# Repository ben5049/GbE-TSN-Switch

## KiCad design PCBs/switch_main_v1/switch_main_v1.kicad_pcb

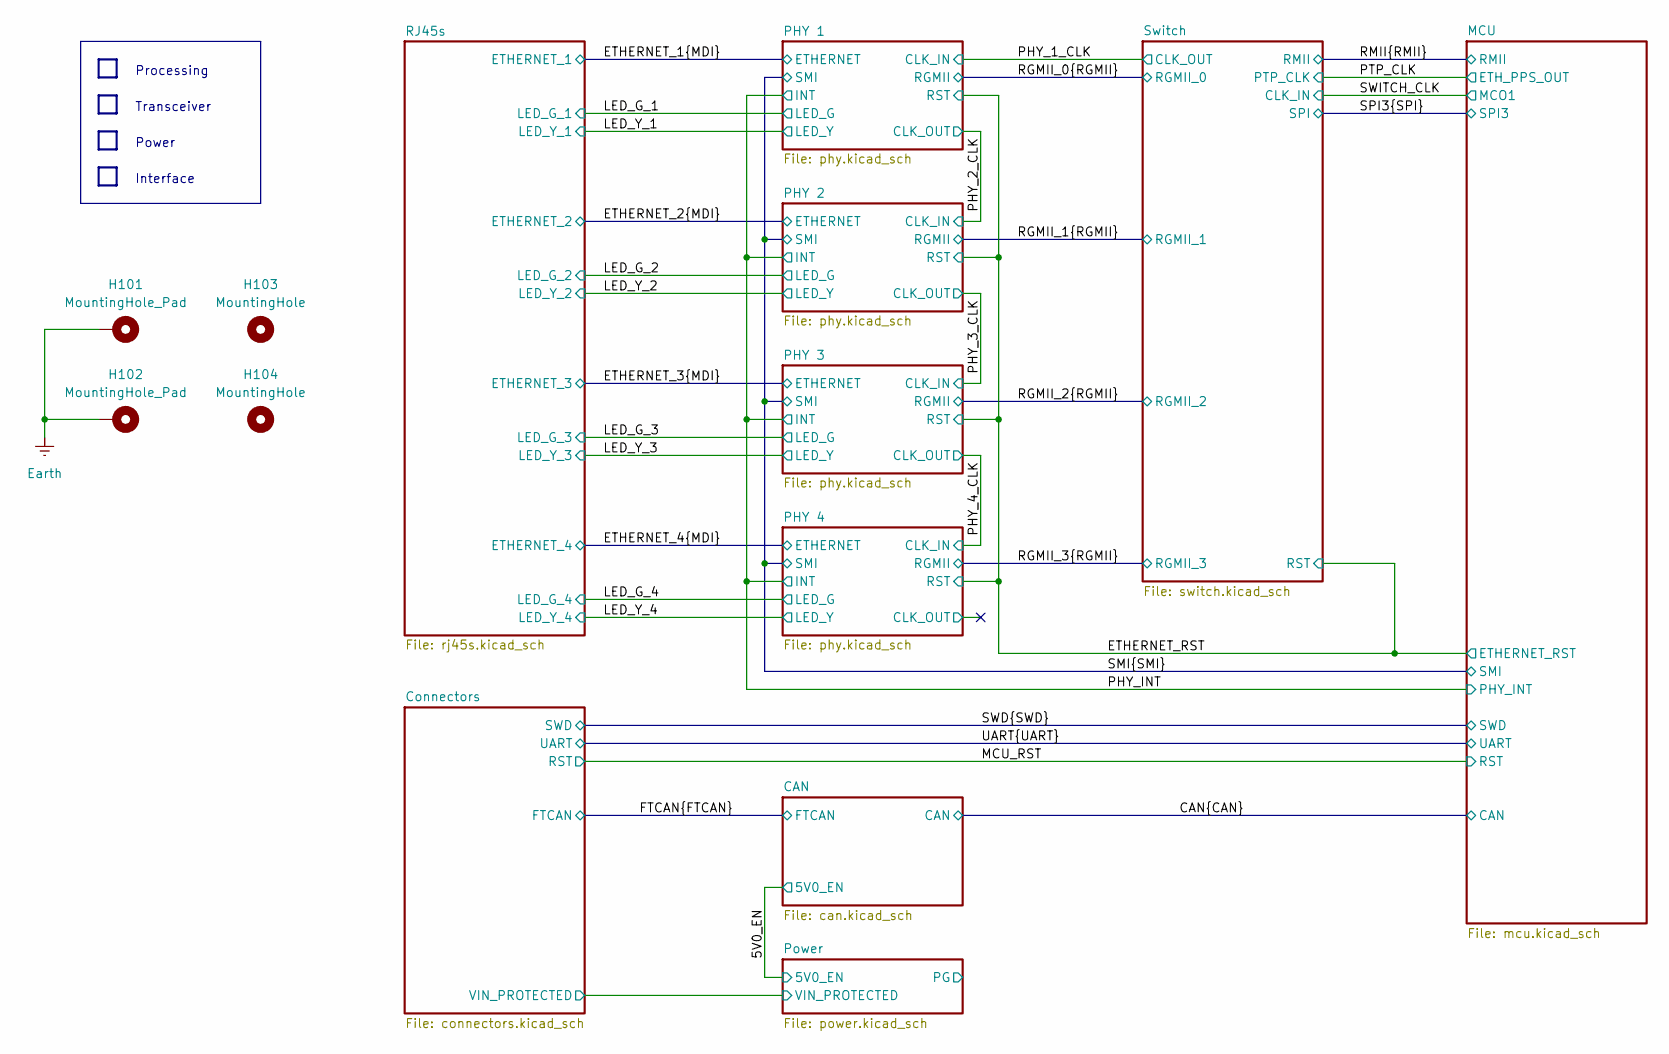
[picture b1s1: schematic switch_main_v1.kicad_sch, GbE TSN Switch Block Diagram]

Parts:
H101, H102: MountingHole_Pad; MountingHole_3.2mm_M3_DIN965_Pad_TopBottom
H103, H104: MountingHole; MountingHole_3.2mm_M3_DIN965

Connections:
Earth: H101.1, H102.1; also elsewhere on the board

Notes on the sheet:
Processing
Power
Interface
Transceiver

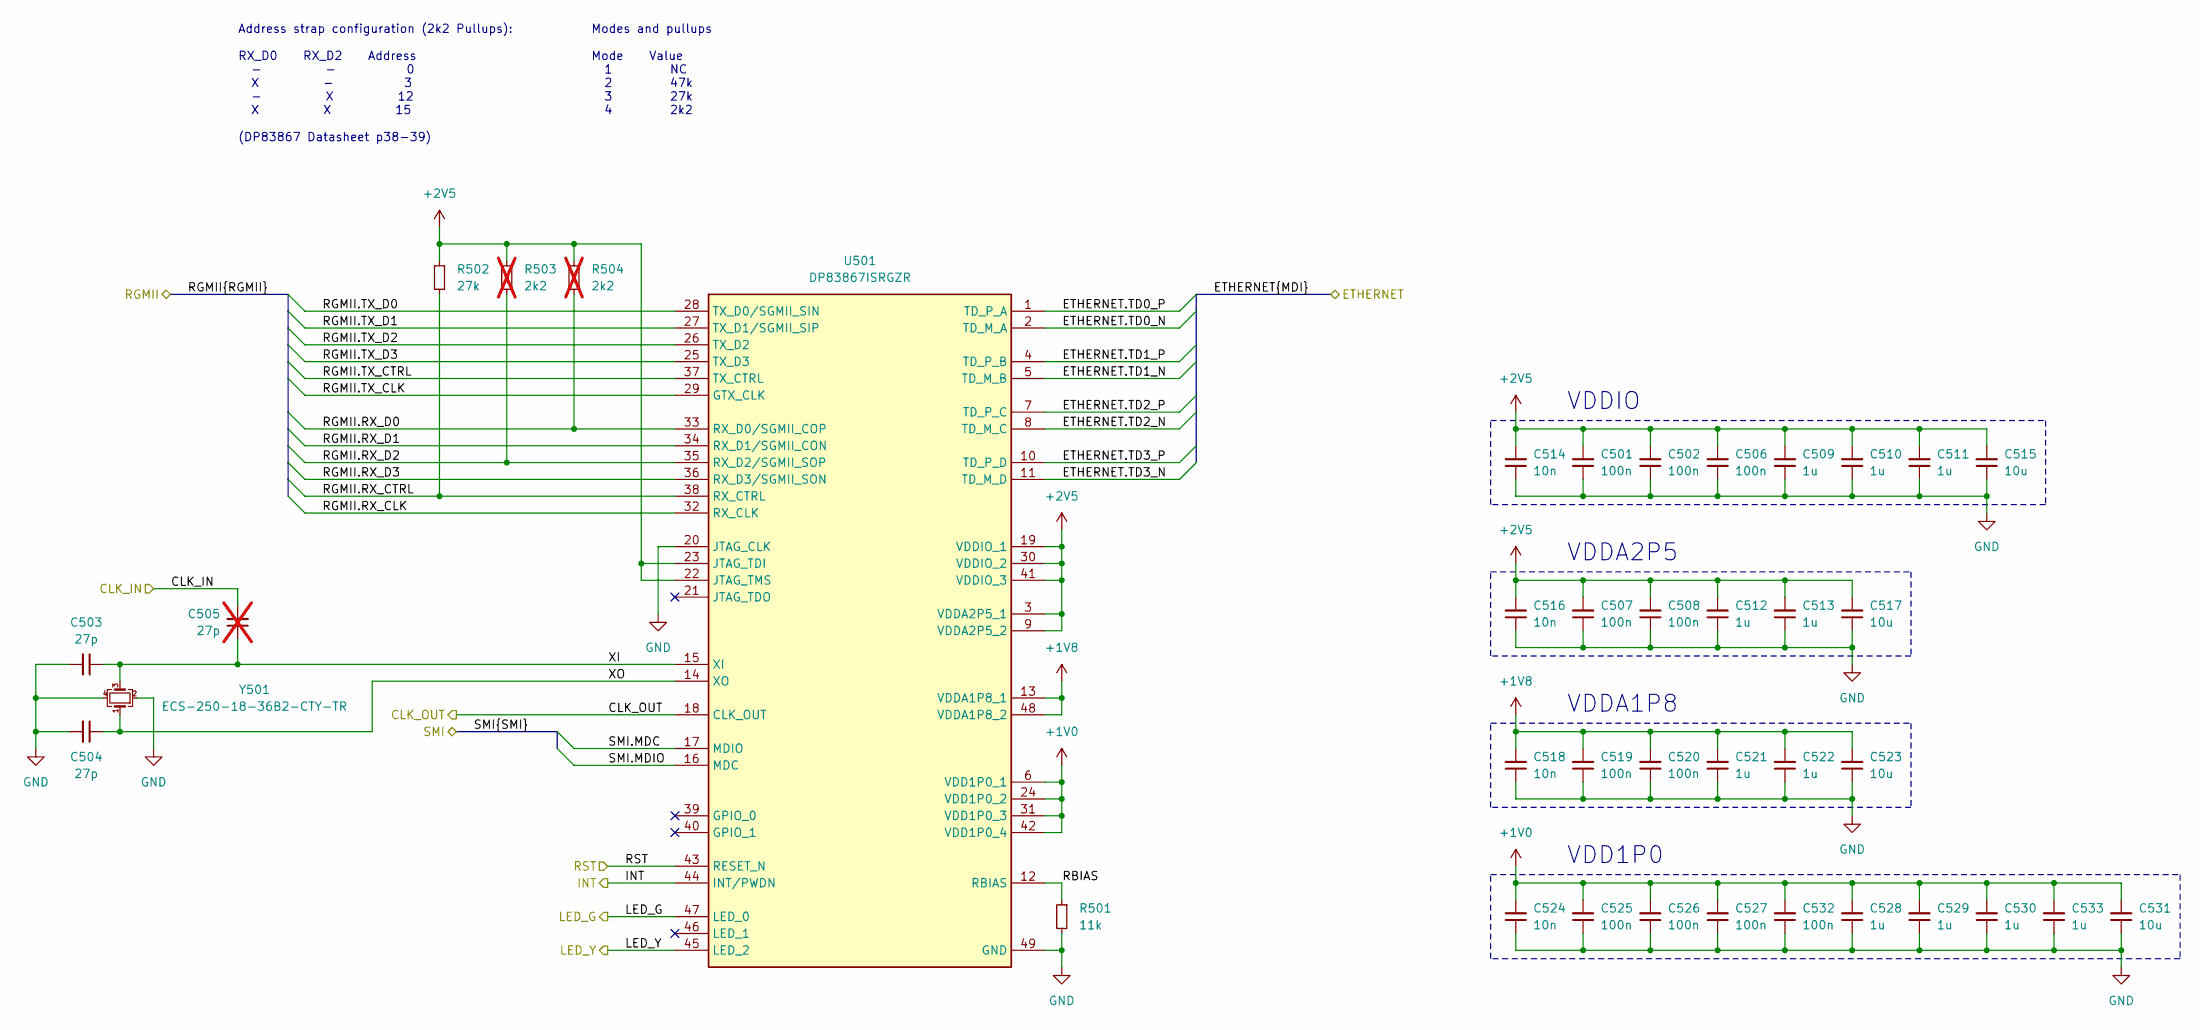
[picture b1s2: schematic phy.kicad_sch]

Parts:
C501, C502, C506, C507, C508, C519, C520, C525, C526, C527, C532: 100n; C_0402_1005Metric
C503, C504: 27p; C_0402_1005Metric
C505: 27p; C_0402_1005Metric; not fitted
C509, C510, C511, C512, C513, C521, C522, C528, C529, C530, C533: 1u; C_0402_1005Metric
C514, C516, C518, C524: 10n; C_0402_1005Metric
C515, C517, C523, C531: 10u; C_0402_1005Metric
R501: 11k; R_0402_1005Metric
R502: 27k; R_0402_1005Metric
R503, R504: 2k2; R_0402_1005Metric; not fitted
U501: DP83867ISRGZR; QFN50P700X700X100-49N-D; Mouser Part Number 595-DP83867CSRGZR
Y501: ECS-250-18-36B2-CTY-TR; Crystal_SMD_2520-4Pin_2.5x2.0mm

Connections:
+1V0: C524.2, C525.2, C526.2, C527.2, C528.2, C529.2, C530.2, C531.2, C532.2, C533.2, U501.6 (VDD1P0_1), U501.24 (VDD1P0_2), U501.31 (VDD1P0_3), U501.42 (VDD1P0_4); also elsewhere on the board
+1V8: C518.2, C519.2, C520.2, C521.2, C522.2, C523.2, U501.13 (VDDA1P8_1), U501.48 (VDDA1P8_2); also elsewhere on the board
+2V5: C501.2, C502.2, C506.2, C507.2, C508.2, C509.2, C510.2, C511.2, C512.2, C513.2, C514.2, C515.2, C516.2, C517.2, R502.1, R503.1, R504.1, U501.3 (VDDA2P5_1), U501.9 (VDDA2P5_2), U501.19 (VDDIO_1), U501.22 (JTAG_TMS), U501.23 (JTAG_TDI), U501.30 (VDDIO_2), U501.41 (VDDIO_3); also elsewhere on the board
/ETHERNET_1.TD0_N: U501.2 (TD_M_A); also elsewhere on the board
/ETHERNET_1.TD0_P: U501.1 (TD_P_A); also elsewhere on the board
/ETHERNET_1.TD1_N: U501.5 (TD_M_B); also elsewhere on the board
/ETHERNET_1.TD1_P: U501.4 (TD_P_B); also elsewhere on the board
/ETHERNET_1.TD2_N: U501.8 (TD_M_C); also elsewhere on the board
/ETHERNET_1.TD2_P: U501.7 (TD_P_C); also elsewhere on the board
/ETHERNET_1.TD3_N: U501.11 (TD_M_D); also elsewhere on the board
/ETHERNET_1.TD3_P: U501.10 (TD_P_D); also elsewhere on the board
/ETHERNET_RST: U501.43 (RESET_N); also elsewhere on the board
/LED_G_1: U501.47 (LED_0); also elsewhere on the board
/LED_Y_1: U501.45 (LED_2); also elsewhere on the board
/PHY 1/RBIAS: R501.1, U501.12 (RBIAS)
/PHY 1/XI: C503.1, C505.1, U501.15 (XI), Y501.3
/PHY 1/XO: C504.1, U501.14 (XO), Y501.1
/PHY_1_CLK: C505.2; also elsewhere on the board
/PHY_2_CLK: U501.18 (CLK_OUT); also elsewhere on the board
/PHY_INT: U501.44 (INT/PWDN); also elsewhere on the board
/RGMII_0.RX_CLK: U501.32 (RX_CLK); also elsewhere on the board
/RGMII_0.RX_CTRL: R502.2, U501.38 (RX_CTRL); also elsewhere on the board
/RGMII_0.RX_D0: R504.2, U501.33 (RX_D0/SGMII_COP); also elsewhere on the board
/RGMII_0.RX_D1: U501.34 (RX_D1/SGMII_CON); also elsewhere on the board
/RGMII_0.RX_D2: R503.2, U501.35 (RX_D2/SGMII_SOP); also elsewhere on the board
/RGMII_0.RX_D3: U501.36 (RX_D3/SGMII_SON); also elsewhere on the board
/RGMII_0.TX_CLK: U501.29 (GTX_CLK); also elsewhere on the board
/RGMII_0.TX_CTRL: U501.37 (TX_CTRL); also elsewhere on the board
/RGMII_0.TX_D0: U501.28 (TX_D0/SGMII_SIN); also elsewhere on the board
/RGMII_0.TX_D1: U501.27 (TX_D1/SGMII_SIP); also elsewhere on the board
/RGMII_0.TX_D2: U501.26 (TX_D2); also elsewhere on the board
/RGMII_0.TX_D3: U501.25 (TX_D3); also elsewhere on the board
/SMI.MDC: U501.17 (MDIO); also elsewhere on the board
/SMI.MDIO: U501.16 (MDC); also elsewhere on the board
GND: C501.1, C502.1, C503.2, C504.2, C506.1, C507.1, C508.1, C509.1, C510.1, C511.1, C512.1, C513.1, C514.1, C515.1, C516.1, C517.1, C518.1, C519.1, C520.1, C521.1, C522.1, C523.1, C524.1, C525.1, C526.1, C527.1, C528.1, C529.1, C530.1, C531.1, C532.1, C533.1, R501.2, U501.20 (JTAG_CLK), U501.49 (GND), Y501.2, Y501.4; also elsewhere on the board

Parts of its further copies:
C601, C602, C606, C607, C608, C619, C620, C625, C626, C627, C632, C701, C702, C706, C707, C708, C719, C720, C725, C726, C727, C732, C801, C802, C806, C807, C808, C819, C820, C825, C826, C827, C832: 100n; C_0402_1005Metric
C603, C604, C703, C704, C803, C804: 27p; C_0402_1005Metric
C605, C705, C805: 27p; C_0402_1005Metric; not fitted
C609, C610, C611, C612, C613, C621, C622, C628, C629, C630, C633, C709, C710, C711, C712, C713, C721, C722, C728, C729, C730, C733, C809, C810, C811, C812, C813, C821, C822, C828, C829, C830, C833: 1u; C_0402_1005Metric
C614, C616, C618, C624, C714, C716, C718, C724, C814, C816, C818, C824: 10n; C_0402_1005Metric
C615, C617, C623, C631, C715, C717, C723, C731, C815, C817, C823, C831: 10u; C_0402_1005Metric
R601, R701, R801: 11k; R_0402_1005Metric
R602, R702, R802: 27k; R_0402_1005Metric
R603, R604, R703, R704, R803, R804: 2k2; R_0402_1005Metric; not fitted
U601, U701, U801: DP83867ISRGZR; QFN50P700X700X100-49N-D; Mouser Part Number 595-DP83867CSRGZR
Y601, Y701, Y801: ECS-250-18-36B2-CTY-TR; Crystal_SMD_2520-4Pin_2.5x2.0mm

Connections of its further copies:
+1V0: C624.2, C625.2, C626.2, C627.2, C628.2, C629.2, C630.2, C631.2, C632.2, C633.2, C724.2, C725.2, C726.2, C727.2, C728.2, C729.2, C730.2, C731.2, C732.2, C733.2, C824.2, C825.2, C826.2, C827.2, C828.2, C829.2, C830.2, C831.2, C832.2, C833.2, U601.6 (VDD1P0_1), U601.24 (VDD1P0_2), U601.31 (VDD1P0_3), U601.42 (VDD1P0_4), U701.6 (VDD1P0_1), U701.24 (VDD1P0_2), U701.31 (VDD1P0_3), U701.42 (VDD1P0_4), U801.6 (VDD1P0_1), U801.24 (VDD1P0_2), U801.31 (VDD1P0_3), U801.42 (VDD1P0_4); also elsewhere on the board
+1V8: C618.2, C619.2, C620.2, C621.2, C622.2, C623.2, C718.2, C719.2, C720.2, C721.2, C722.2, C723.2, C818.2, C819.2, C820.2, C821.2, C822.2, C823.2, U601.13 (VDDA1P8_1), U601.48 (VDDA1P8_2), U701.13 (VDDA1P8_1), U701.48 (VDDA1P8_2), U801.13 (VDDA1P8_1), U801.48 (VDDA1P8_2); also elsewhere on the board
+2V5: C601.2, C602.2, C606.2, C607.2, C608.2, C609.2, C610.2, C611.2, C612.2, C613.2, C614.2, C615.2, C616.2, C617.2, C701.2, C702.2, C706.2, C707.2, C708.2, C709.2, C710.2, C711.2, C712.2, C713.2, C714.2, C715.2, C716.2, C717.2, C801.2, C802.2, C806.2, C807.2, C808.2, C809.2, C810.2, C811.2, C812.2, C813.2, C814.2, C815.2, C816.2, C817.2, R602.1, R603.1, R604.1, R702.1, R703.1, R704.1, R802.1, R803.1, R804.1, U601.3 (VDDA2P5_1), U601.9 (VDDA2P5_2), U601.19 (VDDIO_1), U601.22 (JTAG_TMS), U601.23 (JTAG_TDI), U601.30 (VDDIO_2), U601.41 (VDDIO_3), U701.3 (VDDA2P5_1), U701.9 (VDDA2P5_2), U701.19 (VDDIO_1), U701.22 (JTAG_TMS), U701.23 (JTAG_TDI), U701.30 (VDDIO_2), U701.41 (VDDIO_3), U801.3 (VDDA2P5_1), U801.9 (VDDA2P5_2), U801.19 (VDDIO_1), U801.22 (JTAG_TMS), U801.23 (JTAG_TDI), U801.30 (VDDIO_2), U801.41 (VDDIO_3); also elsewhere on the board
/ETHERNET_2.TD0_N: U601.2 (TD_M_A); also elsewhere on the board
/ETHERNET_2.TD0_P: U601.1 (TD_P_A); also elsewhere on the board
/ETHERNET_2.TD1_N: U601.5 (TD_M_B); also elsewhere on the board
/ETHERNET_2.TD1_P: U601.4 (TD_P_B); also elsewhere on the board
/ETHERNET_2.TD2_N: U601.8 (TD_M_C); also elsewhere on the board
/ETHERNET_2.TD2_P: U601.7 (TD_P_C); also elsewhere on the board
/ETHERNET_2.TD3_N: U601.11 (TD_M_D); also elsewhere on the board
/ETHERNET_2.TD3_P: U601.10 (TD_P_D); also elsewhere on the board
/ETHERNET_3.TD0_N: U701.2 (TD_M_A); also elsewhere on the board
/ETHERNET_3.TD0_P: U701.1 (TD_P_A); also elsewhere on the board
/ETHERNET_3.TD1_N: U701.5 (TD_M_B); also elsewhere on the board
/ETHERNET_3.TD1_P: U701.4 (TD_P_B); also elsewhere on the board
/ETHERNET_3.TD2_N: U701.8 (TD_M_C); also elsewhere on the board
/ETHERNET_3.TD2_P: U701.7 (TD_P_C); also elsewhere on the board
/ETHERNET_3.TD3_N: U701.11 (TD_M_D); also elsewhere on the board
/ETHERNET_3.TD3_P: U701.10 (TD_P_D); also elsewhere on the board
/ETHERNET_4.TD0_N: U801.2 (TD_M_A); also elsewhere on the board
/ETHERNET_4.TD0_P: U801.1 (TD_P_A); also elsewhere on the board
/ETHERNET_4.TD1_N: U801.5 (TD_M_B); also elsewhere on the board
/ETHERNET_4.TD1_P: U801.4 (TD_P_B); also elsewhere on the board
/ETHERNET_4.TD2_N: U801.8 (TD_M_C); also elsewhere on the board
/ETHERNET_4.TD2_P: U801.7 (TD_P_C); also elsewhere on the board
/ETHERNET_4.TD3_N: U801.11 (TD_M_D); also elsewhere on the board
/ETHERNET_4.TD3_P: U801.10 (TD_P_D); also elsewhere on the board
/ETHERNET_RST: U601.43 (RESET_N), U701.43 (RESET_N), U801.43 (RESET_N); also elsewhere on the board
/LED_G_2: U601.47 (LED_0); also elsewhere on the board
/LED_G_3: U701.47 (LED_0); also elsewhere on the board
/LED_G_4: U801.47 (LED_0); also elsewhere on the board
/LED_Y_2: U601.45 (LED_2); also elsewhere on the board
/LED_Y_3: U701.45 (LED_2); also elsewhere on the board
/LED_Y_4: U801.45 (LED_2); also elsewhere on the board
/PHY 2/RBIAS: R601.1, U601.12 (RBIAS)
/PHY 2/XI: C603.1, C605.1, U601.15 (XI), Y601.3
/PHY 2/XO: C604.1, U601.14 (XO), Y601.1
/PHY 3/RBIAS: R701.1, U701.12 (RBIAS)
/PHY 3/XI: C703.1, C705.1, U701.15 (XI), Y701.3
/PHY 3/XO: C704.1, U701.14 (XO), Y701.1
/PHY 4/CLK_OUT: U801.18 (CLK_OUT)
/PHY 4/RBIAS: R801.1, U801.12 (RBIAS)
/PHY 4/XI: C803.1, C805.1, U801.15 (XI), Y801.3
/PHY 4/XO: C804.1, U801.14 (XO), Y801.1
/PHY_2_CLK: C605.2; also elsewhere on the board
/PHY_3_CLK: C705.2, U601.18 (CLK_OUT)
/PHY_4_CLK: C805.2, U701.18 (CLK_OUT)
/PHY_INT: U601.44 (INT/PWDN), U701.44 (INT/PWDN), U801.44 (INT/PWDN); also elsewhere on the board
/RGMII_1.RX_CLK: U601.32 (RX_CLK); also elsewhere on the board
/RGMII_1.RX_CTRL: R602.2, U601.38 (RX_CTRL); also elsewhere on the board
/RGMII_1.RX_D0: R604.2, U601.33 (RX_D0/SGMII_COP); also elsewhere on the board
/RGMII_1.RX_D1: U601.34 (RX_D1/SGMII_CON); also elsewhere on the board
/RGMII_1.RX_D2: R603.2, U601.35 (RX_D2/SGMII_SOP); also elsewhere on the board
/RGMII_1.RX_D3: U601.36 (RX_D3/SGMII_SON); also elsewhere on the board
/RGMII_1.TX_CLK: U601.29 (GTX_CLK); also elsewhere on the board
/RGMII_1.TX_CTRL: U601.37 (TX_CTRL); also elsewhere on the board
/RGMII_1.TX_D0: U601.28 (TX_D0/SGMII_SIN); also elsewhere on the board
/RGMII_1.TX_D1: U601.27 (TX_D1/SGMII_SIP); also elsewhere on the board
/RGMII_1.TX_D2: U601.26 (TX_D2); also elsewhere on the board
/RGMII_1.TX_D3: U601.25 (TX_D3); also elsewhere on the board
/RGMII_2.RX_CLK: U701.32 (RX_CLK); also elsewhere on the board
/RGMII_2.RX_CTRL: R702.2, U701.38 (RX_CTRL); also elsewhere on the board
/RGMII_2.RX_D0: R704.2, U701.33 (RX_D0/SGMII_COP); also elsewhere on the board
/RGMII_2.RX_D1: U701.34 (RX_D1/SGMII_CON); also elsewhere on the board
/RGMII_2.RX_D2: R703.2, U701.35 (RX_D2/SGMII_SOP); also elsewhere on the board
/RGMII_2.RX_D3: U701.36 (RX_D3/SGMII_SON); also elsewhere on the board
/RGMII_2.TX_CLK: U701.29 (GTX_CLK); also elsewhere on the board
/RGMII_2.TX_CTRL: U701.37 (TX_CTRL); also elsewhere on the board
/RGMII_2.TX_D0: U701.28 (TX_D0/SGMII_SIN); also elsewhere on the board
/RGMII_2.TX_D1: U701.27 (TX_D1/SGMII_SIP); also elsewhere on the board
/RGMII_2.TX_D2: U701.26 (TX_D2); also elsewhere on the board
/RGMII_2.TX_D3: U701.25 (TX_D3); also elsewhere on the board
/RGMII_3.RX_CLK: U801.32 (RX_CLK); also elsewhere on the board
/RGMII_3.RX_CTRL: R802.2, U801.38 (RX_CTRL); also elsewhere on the board
/RGMII_3.RX_D0: R804.2, U801.33 (RX_D0/SGMII_COP); also elsewhere on the board
/RGMII_3.RX_D1: U801.34 (RX_D1/SGMII_CON); also elsewhere on the board
/RGMII_3.RX_D2: R803.2, U801.35 (RX_D2/SGMII_SOP); also elsewhere on the board
/RGMII_3.RX_D3: U801.36 (RX_D3/SGMII_SON); also elsewhere on the board
/RGMII_3.TX_CLK: U801.29 (GTX_CLK); also elsewhere on the board
/RGMII_3.TX_CTRL: U801.37 (TX_CTRL); also elsewhere on the board
/RGMII_3.TX_D0: U801.28 (TX_D0/SGMII_SIN); also elsewhere on the board
/RGMII_3.TX_D1: U801.27 (TX_D1/SGMII_SIP); also elsewhere on the board
/RGMII_3.TX_D2: U801.26 (TX_D2); also elsewhere on the board
/RGMII_3.TX_D3: U801.25 (TX_D3); also elsewhere on the board
/SMI.MDC: U601.17 (MDIO), U701.17 (MDIO), U801.17 (MDIO); also elsewhere on the board
/SMI.MDIO: U601.16 (MDC), U701.16 (MDC), U801.16 (MDC); also elsewhere on the board
GND: C601.1, C602.1, C603.2, C604.2, C606.1, C607.1, C608.1, C609.1, C610.1, C611.1, C612.1, C613.1, C614.1, C615.1, C616.1, C617.1, C618.1, C619.1, C620.1, C621.1, C622.1, C623.1, C624.1, C625.1, C626.1, C627.1, C628.1, C629.1, C630.1, C631.1, C632.1, C633.1, C701.1, C702.1, C703.2, C704.2, C706.1, C707.1, C708.1, C709.1, C710.1, C711.1, C712.1, C713.1, C714.1, C715.1, C716.1, C717.1, C718.1, C719.1, C720.1, C721.1, C722.1, C723.1, C724.1, C725.1, C726.1, C727.1, C728.1, C729.1, C730.1, C731.1, C732.1, C733.1, C801.1, C802.1, C803.2, C804.2, C806.1, C807.1, C808.1, C809.1, C810.1, C811.1, C812.1, C813.1, C814.1, C815.1, C816.1, C817.1, C818.1, C819.1, C820.1, C821.1, C822.1, C823.1, C824.1, C825.1, C826.1, C827.1, C828.1, C829.1, C830.1, C831.1, C832.1, C833.1, R601.2, R701.2, R801.2, U601.20 (JTAG_CLK), U601.49 (GND), U701.20 (JTAG_CLK), U701.49 (GND), U801.20 (JTAG_CLK), U801.49 (GND), Y601.2, Y601.4, Y701.2, Y701.4, Y801.2, Y801.4; also elsewhere on the board

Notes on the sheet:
VDDIO
VDD1P0
Address strap configuration (2k2 Pullups): RX_D0 RX_D2 Address - - 0 X - 3 - X 12 X X 15 (DP83867 Datasheet p38-39)
VDDA1P8
VDDA2P5
Modes and pullups Mode Value 1 NC 2 47k 3 27k 4 2k2

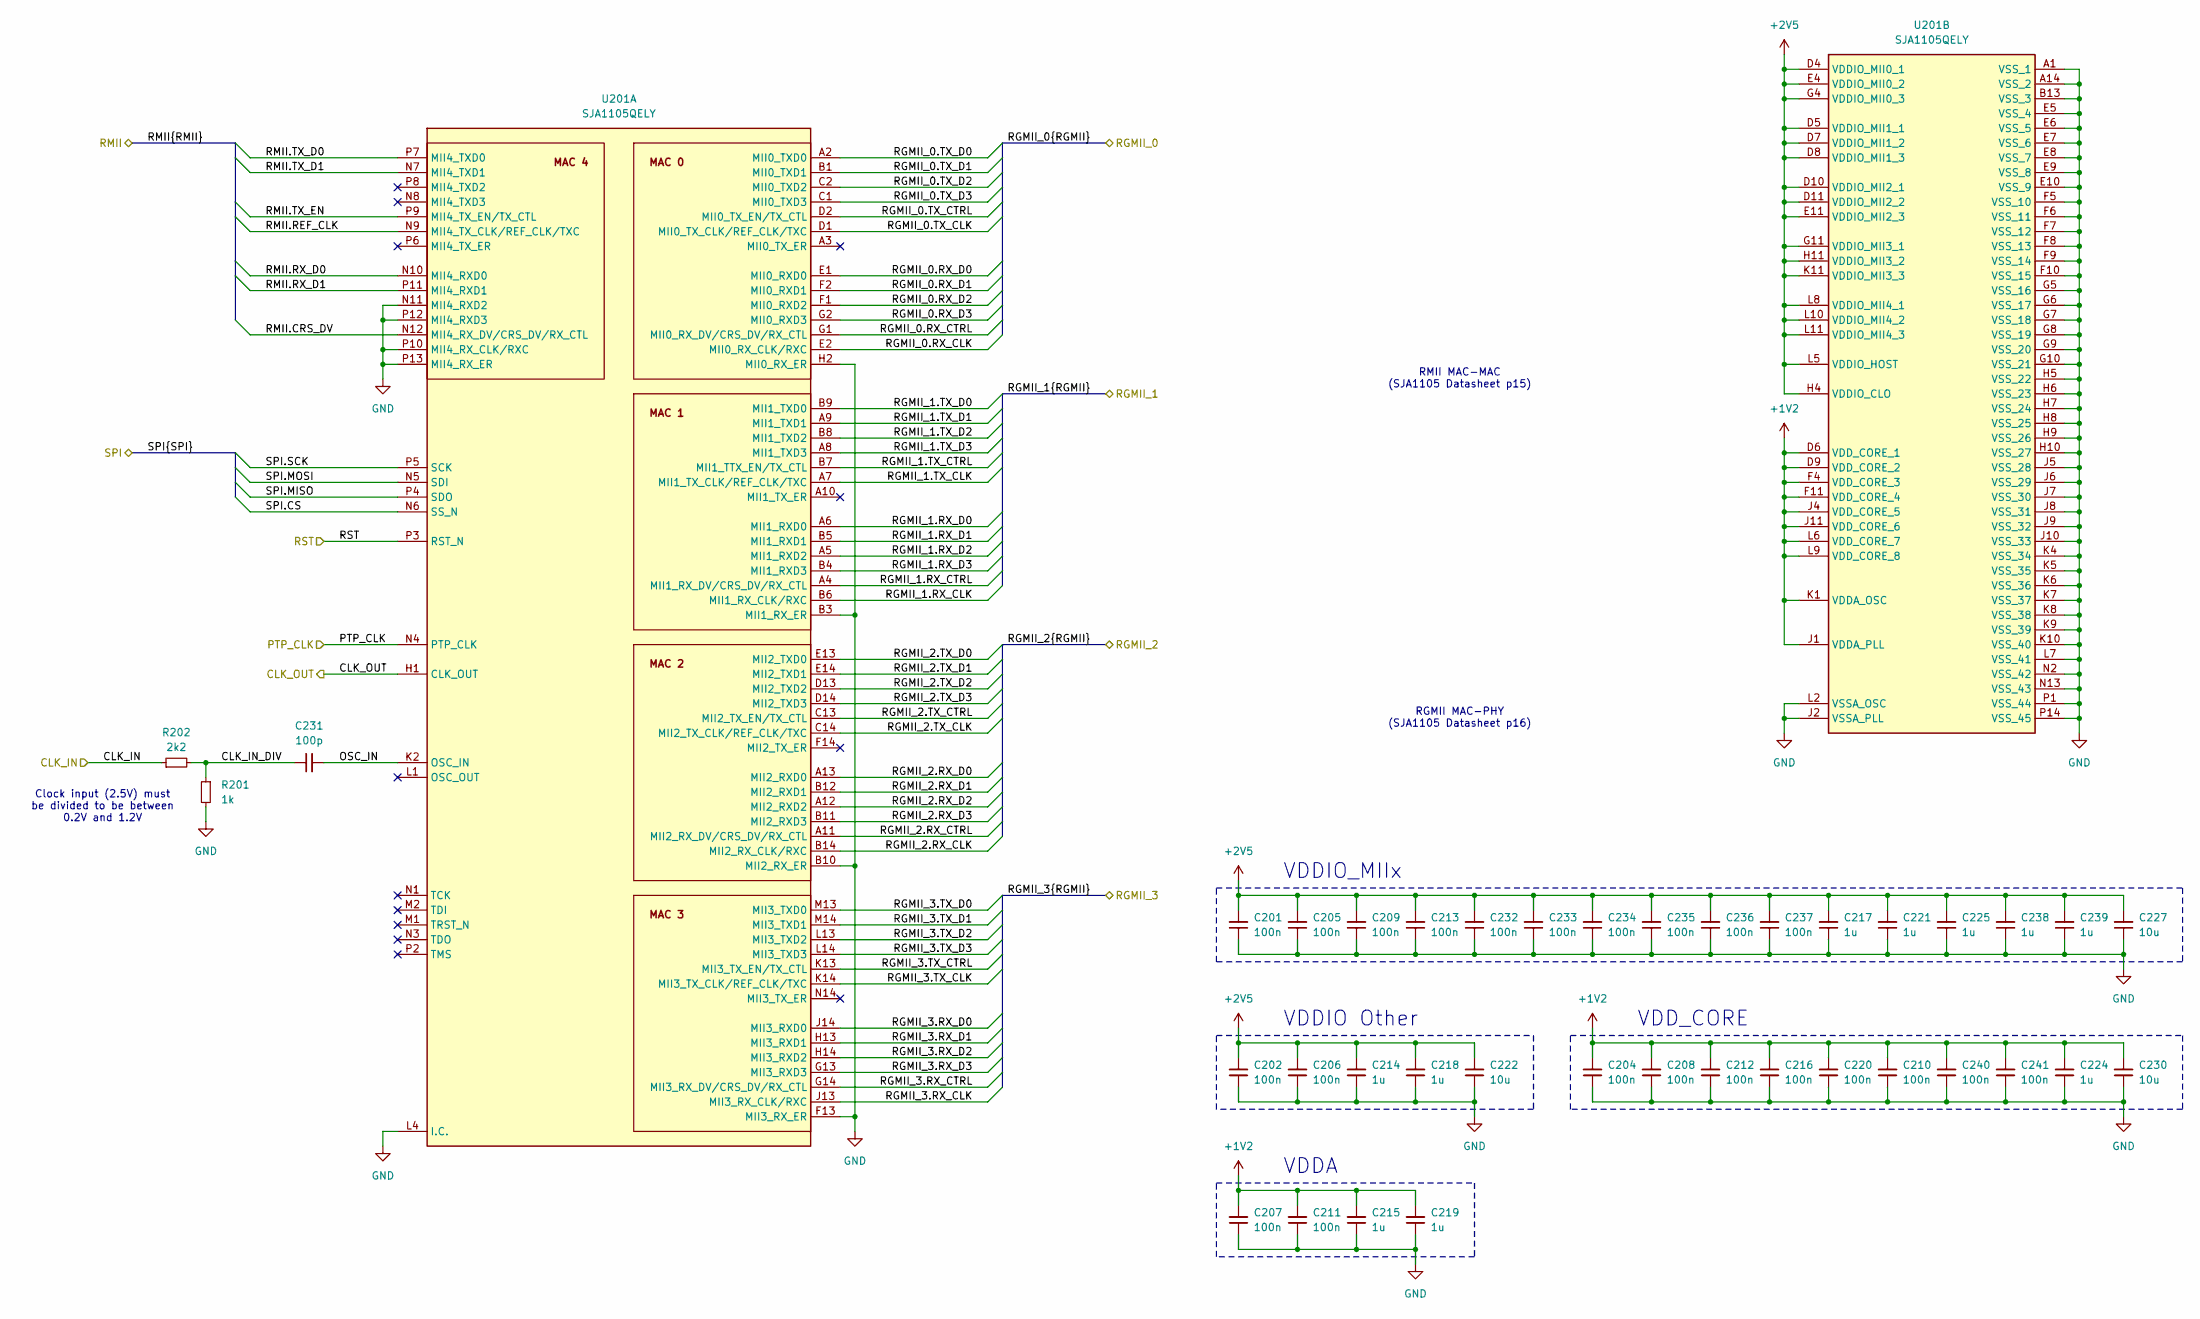
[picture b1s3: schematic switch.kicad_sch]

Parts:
C201, C202, C204, C205, C206, C207, C208, C209, C210, C211, C212, C213, C216, C220, C232, C233, C234, C235, C236, C237, C240, C241: 100n; C_0402_1005Metric
C214, C215, C217, C218, C219, C221, C224, C225, C238, C239: 1u; C_0402_1005Metric
C222, C227, C230: 10u; C_0402_1005Metric
C231: 100p; C_0402_1005Metric
R201: 1k; R_0402_1005Metric
R202: 2k2; R_0402_1005Metric
U201: SJA1105QELY; BGA159C80P14X14_1200X1200X150; Mouser Part Number 771-SJA1105QELY

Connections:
+1V2: C204.2, C207.2, C208.2, C210.2, C211.2, C212.2, C215.2, C216.2, C219.2, C220.2, C224.2, C230.2, C240.2, C241.2, U201.D6 (VDD_CORE_1), U201.D9 (VDD_CORE_2), U201.F4 (VDD_CORE_3), U201.F11 (VDD_CORE_4), U201.J1 (VDDA_PLL), U201.J4 (VDD_CORE_5), U201.J11 (VDD_CORE_6), U201.K1 (VDDA_OSC), U201.L6 (VDD_CORE_7), U201.L9 (VDD_CORE_8)
+2V5: C201.2, C202.2, C205.2, C206.2, C209.2, C213.2, C214.2, C217.2, C218.2, C221.2, C222.2, C225.2, C227.2, C232.2, C233.2, C234.2, C235.2, C236.2, C237.2, C238.2, C239.2, U201.D4 (VDDIO_MII0_1), U201.D5 (VDDIO_MII1_1), U201.D7 (VDDIO_MII1_2), U201.D8 (VDDIO_MII1_3), U201.D10 (VDDIO_MII2_1), U201.D11 (VDDIO_MII2_2), U201.E4 (VDDIO_MII0_2), U201.E11 (VDDIO_MII2_3), U201.G4 (VDDIO_MII0_3), U201.G11 (VDDIO_MII3_1), U201.H4 (VDDIO_CLO), U201.H11 (VDDIO_MII3_2), U201.K11 (VDDIO_MII3_3), U201.L5 (VDDIO_HOST), U201.L8 (VDDIO_MII4_1), U201.L10 (VDDIO_MII4_2), U201.L11 (VDDIO_MII4_3); also elsewhere on the board
/ETHERNET_RST: U201.P3 (RST_N); also elsewhere on the board
/PHY_1_CLK: U201.H1 (CLK_OUT); also elsewhere on the board
/PTP_CLK: U201.N4 (PTP_CLK); also elsewhere on the board
/RGMII_0.RX_CLK: U201.E2 (MII0_RX_CLK/RXC); also elsewhere on the board
/RGMII_0.RX_CTRL: U201.G1 (MII0_RX_DV/CRS_DV/RX_CTL); also elsewhere on the board
/RGMII_0.RX_D0: U201.E1 (MII0_RXD0); also elsewhere on the board
/RGMII_0.RX_D1: U201.F2 (MII0_RXD1); also elsewhere on the board
/RGMII_0.RX_D2: U201.F1 (MII0_RXD2); also elsewhere on the board
/RGMII_0.RX_D3: U201.G2 (MII0_RXD3); also elsewhere on the board
/RGMII_0.TX_CLK: U201.D1 (MII0_TX_CLK/REF_CLK/TXC); also elsewhere on the board
/RGMII_0.TX_CTRL: U201.D2 (MII0_TX_EN/TX_CTL); also elsewhere on the board
/RGMII_0.TX_D0: U201.A2 (MII0_TXD0); also elsewhere on the board
/RGMII_0.TX_D1: U201.B1 (MII0_TXD1); also elsewhere on the board
/RGMII_0.TX_D2: U201.C2 (MII0_TXD2); also elsewhere on the board
/RGMII_0.TX_D3: U201.C1 (MII0_TXD3); also elsewhere on the board
/RGMII_1.RX_CLK: U201.B6 (MII1_RX_CLK/RXC); also elsewhere on the board
/RGMII_1.RX_CTRL: U201.A4 (MII1_RX_DV/CRS_DV/RX_CTL); also elsewhere on the board
/RGMII_1.RX_D0: U201.A6 (MII1_RXD0); also elsewhere on the board
/RGMII_1.RX_D1: U201.B5 (MII1_RXD1); also elsewhere on the board
/RGMII_1.RX_D2: U201.A5 (MII1_RXD2); also elsewhere on the board
/RGMII_1.RX_D3: U201.B4 (MII1_RXD3); also elsewhere on the board
/RGMII_1.TX_CLK: U201.A7 (MII1_TX_CLK/REF_CLK/TXC); also elsewhere on the board
/RGMII_1.TX_CTRL: U201.B7 (MII1_TTX_EN/TX_CTL); also elsewhere on the board
/RGMII_1.TX_D0: U201.B9 (MII1_TXD0); also elsewhere on the board
/RGMII_1.TX_D1: U201.A9 (MII1_TXD1); also elsewhere on the board
/RGMII_1.TX_D2: U201.B8 (MII1_TXD2); also elsewhere on the board
/RGMII_1.TX_D3: U201.A8 (MII1_TXD3); also elsewhere on the board
/RGMII_2.RX_CLK: U201.B14 (MII2_RX_CLK/RXC); also elsewhere on the board
/RGMII_2.RX_CTRL: U201.A11 (MII2_RX_DV/CRS_DV/RX_CTL); also elsewhere on the board
/RGMII_2.RX_D0: U201.A13 (MII2_RXD0); also elsewhere on the board
/RGMII_2.RX_D1: U201.B12 (MII2_RXD1); also elsewhere on the board
/RGMII_2.RX_D2: U201.A12 (MII2_RXD2); also elsewhere on the board
/RGMII_2.RX_D3: U201.B11 (MII2_RXD3); also elsewhere on the board
/RGMII_2.TX_CLK: U201.C14 (MII2_TX_CLK/REF_CLK/TXC); also elsewhere on the board
/RGMII_2.TX_CTRL: U201.C13 (MII2_TX_EN/TX_CTL); also elsewhere on the board
/RGMII_2.TX_D0: U201.E13 (MII2_TXD0); also elsewhere on the board
/RGMII_2.TX_D1: U201.E14 (MII2_TXD1); also elsewhere on the board
/RGMII_2.TX_D2: U201.D13 (MII2_TXD2); also elsewhere on the board
/RGMII_2.TX_D3: U201.D14 (MII2_TXD3); also elsewhere on the board
/RGMII_3.RX_CLK: U201.J13 (MII3_RX_CLK/RXC); also elsewhere on the board
/RGMII_3.RX_CTRL: U201.G14 (MII3_RX_DV/CRS_DV/RX_CTL); also elsewhere on the board
/RGMII_3.RX_D0: U201.J14 (MII3_RXD0); also elsewhere on the board
/RGMII_3.RX_D1: U201.H13 (MII3_RXD1); also elsewhere on the board
/RGMII_3.RX_D2: U201.H14 (MII3_RXD2); also elsewhere on the board
/RGMII_3.RX_D3: U201.G13 (MII3_RXD3); also elsewhere on the board
/RGMII_3.TX_CLK: U201.K14 (MII3_TX_CLK/REF_CLK/TXC); also elsewhere on the board
/RGMII_3.TX_CTRL: U201.K13 (MII3_TX_EN/TX_CTL); also elsewhere on the board
/RGMII_3.TX_D0: U201.M13 (MII3_TXD0); also elsewhere on the board
/RGMII_3.TX_D1: U201.M14 (MII3_TXD1); also elsewhere on the board
/RGMII_3.TX_D2: U201.L13 (MII3_TXD2); also elsewhere on the board
/RGMII_3.TX_D3: U201.L14 (MII3_TXD3); also elsewhere on the board
/RMII.CRS_DV: U201.N12 (MII4_RX_DV/CRS_DV/RX_CTL); also elsewhere on the board
/RMII.REF_CLK: U201.N9 (MII4_TX_CLK/REF_CLK/TXC); also elsewhere on the board
/RMII.RX_D0: U201.N10 (MII4_RXD0); also elsewhere on the board
/RMII.RX_D1: U201.P11 (MII4_RXD1); also elsewhere on the board
/RMII.TX_D0: U201.P7 (MII4_TXD0); also elsewhere on the board
/RMII.TX_D1: U201.N7 (MII4_TXD1); also elsewhere on the board
/RMII.TX_EN: U201.P9 (MII4_TX_EN/TX_CTL); also elsewhere on the board
/SPI3.CS: U201.N6 (SS_N)
/SPI3.MISO: U201.P4 (SDO)
/SPI3.MOSI: U201.N5 (SDI)
/SPI3.SCK: U201.P5 (SCK)
/SWITCH_CLK: R202.1; also elsewhere on the board
/Switch/CLK_IN_DIV: C231.1, R201.1, R202.2
/Switch/OSC_IN: C231.2, U201.K2 (OSC_IN)
GND: C201.1, C202.1, C204.1, C205.1, C206.1, C207.1, C208.1, C209.1, C210.1, C211.1, C212.1, C213.1, C214.1, C215.1, C216.1, C217.1, C218.1, C219.1, C220.1, C221.1, C222.1, C224.1, C225.1, C227.1, C230.1, C232.1, C233.1, C234.1, C235.1, C236.1, C237.1, C238.1, C239.1, C240.1, C241.1, R201.2, U201.A1 (VSS_1), U201.A14 (VSS_2), U201.B3 (MII1_RX_ER), U201.B10 (MII2_RX_ER), U201.B13 (VSS_3), U201.E5 (VSS_4), U201.E6 (VSS_5), U201.E7 (VSS_6), U201.E8 (VSS_7), U201.E9 (VSS_8), U201.E10 (VSS_9), U201.F5 (VSS_10), U201.F6 (VSS_11), U201.F7 (VSS_12), U201.F8 (VSS_13), U201.F9 (VSS_14), U201.F10 (VSS_15), U201.F13 (MII3_RX_ER), U201.G5 (VSS_16), U201.G6 (VSS_17), U201.G7 (VSS_18), U201.G8 (VSS_19), U201.G9 (VSS_20), U201.G10 (VSS_21), U201.H2 (MII0_RX_ER), U201.H5 (VSS_22), U201.H6 (VSS_23), U201.H7 (VSS_24), U201.H8 (VSS_25), U201.H9 (VSS_26), U201.H10 (VSS_27), U201.J2 (VSSA_PLL), U201.J5 (VSS_28), U201.J6 (VSS_29), U201.J7 (VSS_30), U201.J8 (VSS_31), U201.J9 (VSS_32), U201.J10 (VSS_33), U201.K4 (VSS_34), U201.K5 (VSS_35), U201.K6 (VSS_36), U201.K7 (VSS_37), U201.K8 (VSS_38), U201.K9 (VSS_39), U201.K10 (VSS_40), U201.L2 (VSSA_OSC), U201.L4 (I.C.), U201.L7 (VSS_41), U201.N2 (VSS_42), U201.N11 (MII4_RXD2), U201.N13 (VSS_43), U201.P1 (VSS_44), U201.P10 (MII4_RX_CLK/RXC), U201.P12 (MII4_RXD3), U201.P13 (MII4_RX_ER), U201.P14 (VSS_45); also elsewhere on the board

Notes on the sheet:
VDDIO Other
Clock input (2.5V) must be divided to be between 0.2V and 1.2V
VDDIO_MIIx
RMII MAC-MAC (SJA1105 Datasheet p15)
VDD_CORE
VDDA
RGMII MAC-PHY (SJA1105 Datasheet p16)
